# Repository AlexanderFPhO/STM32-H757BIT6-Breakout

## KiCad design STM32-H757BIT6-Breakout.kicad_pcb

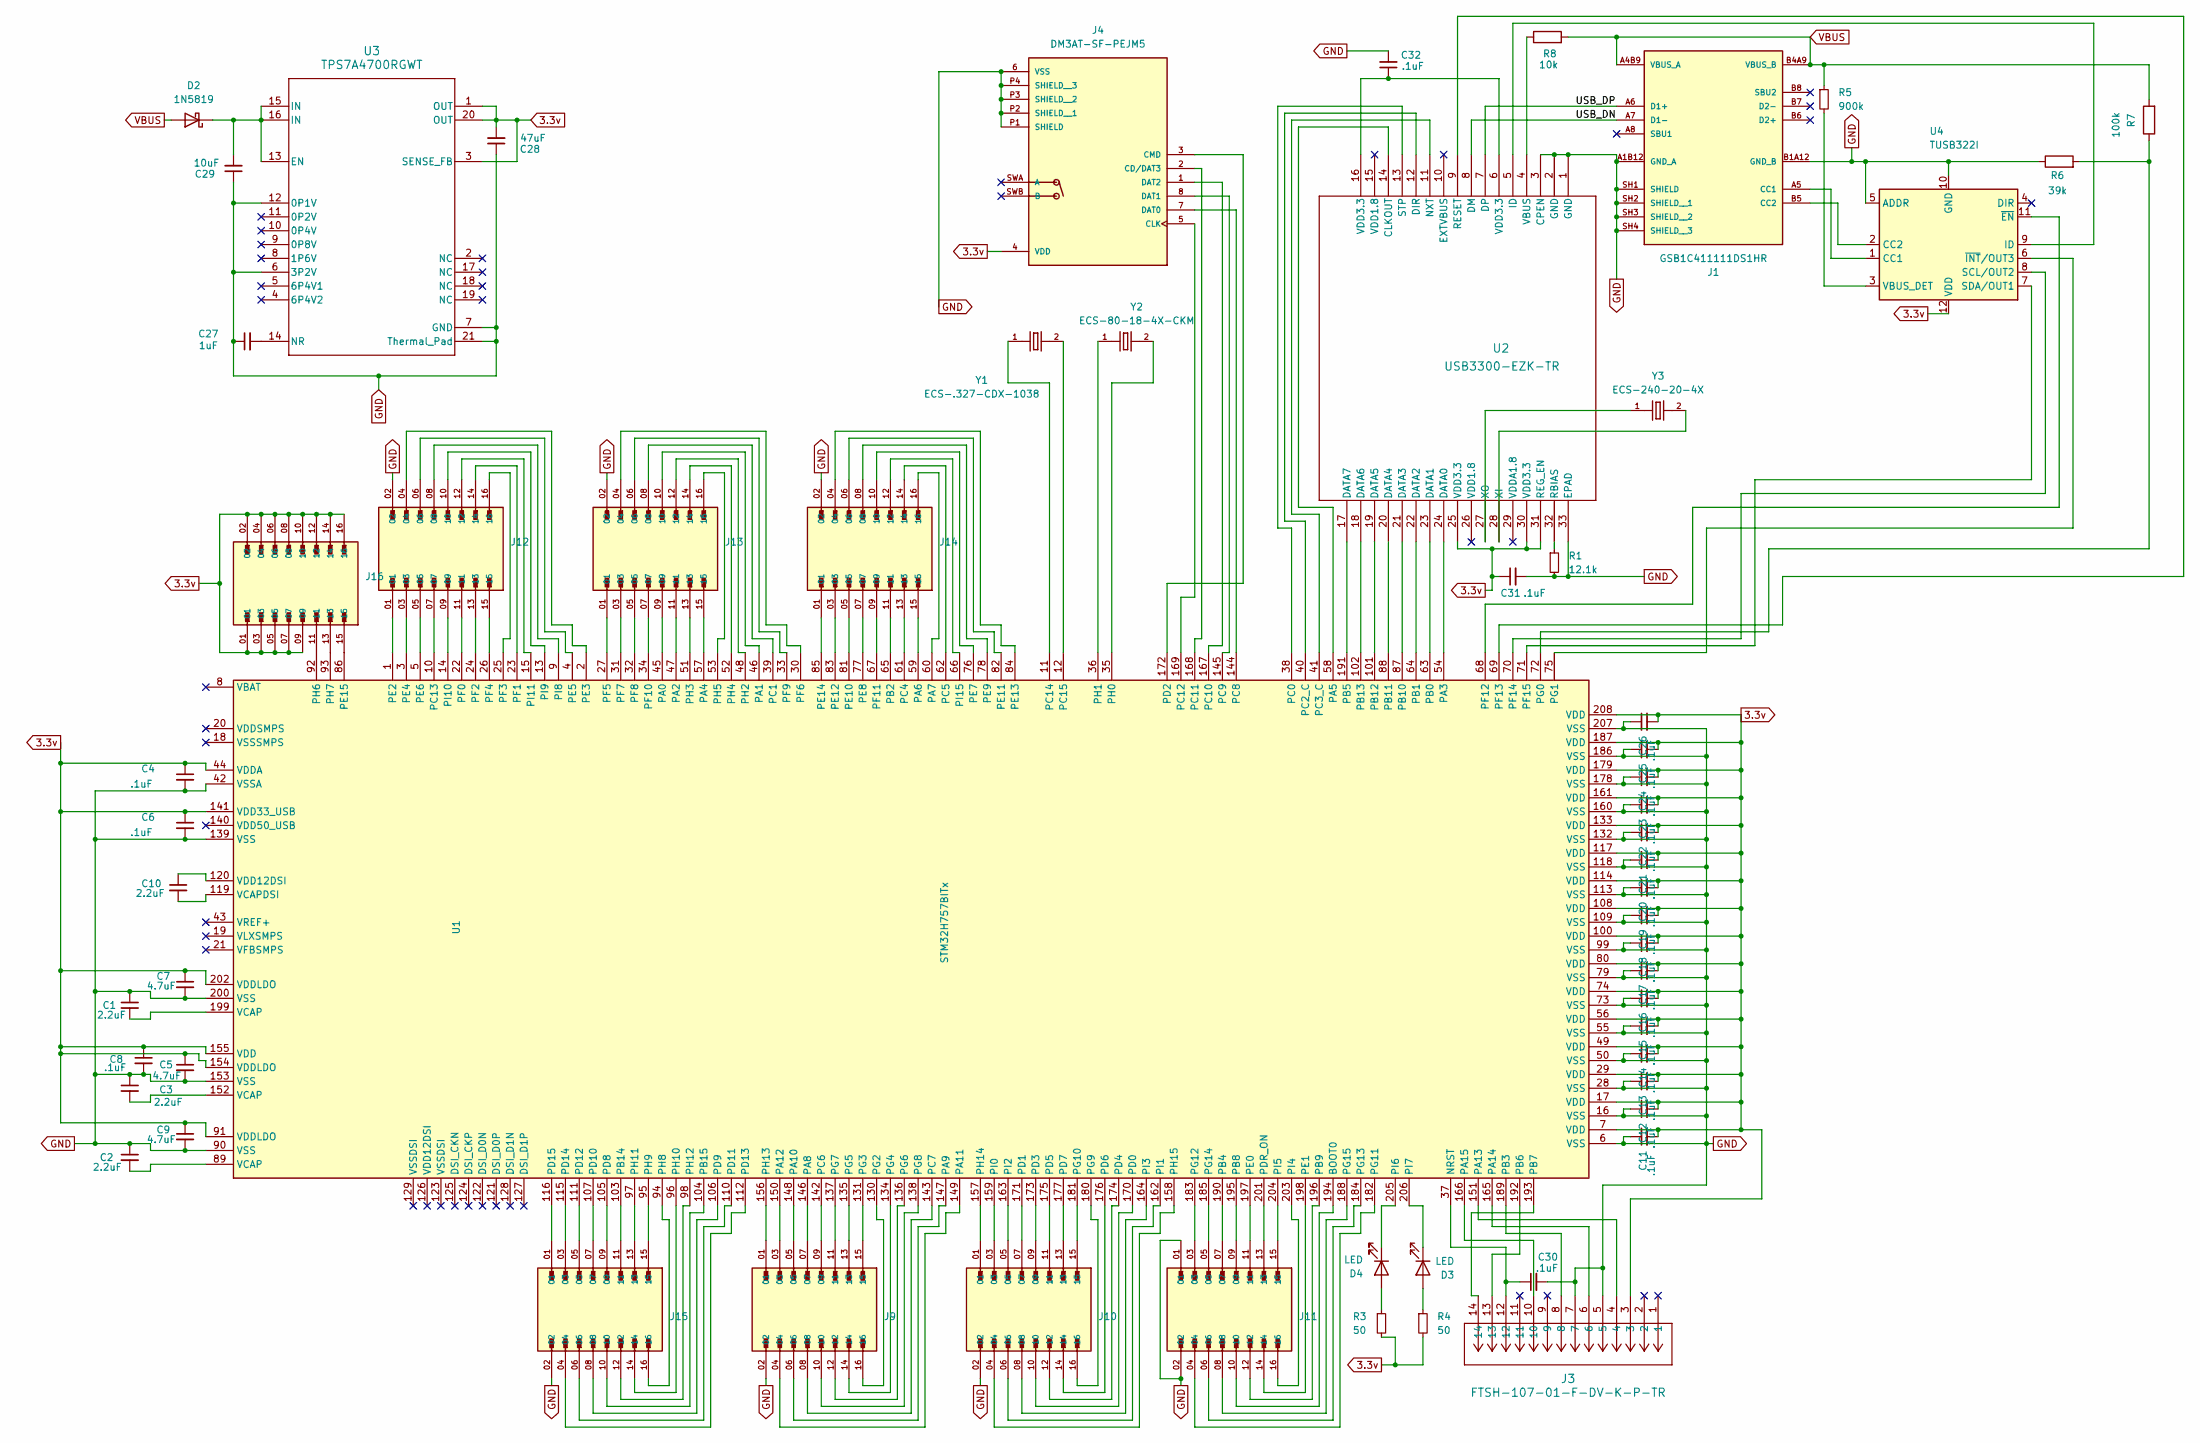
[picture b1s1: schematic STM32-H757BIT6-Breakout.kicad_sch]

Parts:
C1, C2, C3, C10: 2.2uF; C_0603_1608Metric_Pad1.08x0.95mm_HandSolder
C4, C6, C8, C11, C12, C13, C14, C15, C16, C17, C18, C19, C20, C21, C22, C23, C24, C25, C26, C30, C31, C32: .1uF; C_0603_1608Metric_Pad1.08x0.95mm_HandSolder
C5, C7, C9: 4.7uF; C_0603_1608Metric_Pad1.08x0.95mm_HandSolder
C27: 1uF; C_0603_1608Metric_Pad1.08x0.95mm_HandSolder
C28: 47uF; C_0603_1608Metric_Pad1.08x0.95mm_HandSolder
C29: 10uF; C_0603_1608Metric_Pad1.08x0.95mm_HandSolder
D2: 1N5819; D_DO-41_SOD81_P10.16mm_Horizontal
D3, D4: LED; LED_0603_1608Metric_Pad1.05x0.95mm_HandSolder
J1: GSB1C411111DS1HR; GSB1C411111DS1HR_AMPHENOL_GSB1C411111DS1HR; PARTREV AX3
J3: FTSH-107-01-F-DV-K-P-TR; CONN_FTSH-107-01-F-DV-K-P-TR_SAI
J4: DM3AT-SF-PEJM5; DM3AT-SF-PEJM5_HRS_DM3AT-SF-PEJM5; PARTREV 20200913
J9, J10, J11, J12, J13, J14, J15, J16: 10129381-916001BLF; PARTREV D
R1: 12.1k; R_0603_1608Metric_Pad0.98x0.95mm_HandSolder
R3, R4: 50; R_0603_1608Metric_Pad0.98x0.95mm_HandSolder
R5: 900k; R_0603_1608Metric_Pad0.98x0.95mm_HandSolder
R6: 39k; R_0603_1608Metric_Pad0.98x0.95mm_HandSolder
R7: 100k; R_0603_1608Metric_Pad0.98x0.95mm_HandSolder
R8: 10k; R_0603_1608Metric_Pad0.98x0.95mm_HandSolder
U1: STM32H757BITx; LQFP-208_28x28mm_P0.5mm
U2: USB3300-EZK-TR; QFN32_5X5MC_MCH
U3: TPS7A4700RGWT; RGW0020A-IPC_A
U4: TUSB322I; Texas_X2QFN-12_1.6x1.6mm_P0.4mm
Y1: ECS-.327-CDX-1038; ECS-.327-CDX-1038_XTAL_ECS-.327-CDX-1038
Y2: ECS-80-18-4X-CKM; ECS-80-18-4X-CKM_XTAL_ECS-80-18-4X-CKM
Y3: ECS-240-20-4X; ECS-240-20-4X_XTAL_ECS-240-20-4X

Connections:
3.3v: C4.1, C5.1, C6.1, C7.1, C8.1, C9.1, C11.2, C12.2, C13.2, C14.2, C15.2, C16.2, C17.2, C18.2, C19.2, C20.2, C21.2, C22.2, C23.2, C24.2, C25.2, C26.2, C28.2, C31.1, J3.3, J4.4 (VDD), J16.01, J16.02, J16.03, J16.04, J16.05, J16.06, J16.07, J16.08, J16.09, J16.10, J16.12, J16.14, J16.16, R3.2, R4.2, U1.7 (VDD), U1.17 (VDD), U1.29 (VDD), U1.44 (VDDA), U1.49 (VDD), U1.56 (VDD), U1.74 (VDD), U1.80 (VDD), U1.91 (VDDLDO), U1.100 (VDD), U1.108 (VDD), U1.114 (VDD), U1.117 (VDD), U1.133 (VDD), U1.141 (VDD33_USB), U1.154 (VDDLDO), U1.155 (VDD), U1.161 (VDD), U1.179 (VDD), U1.187 (VDD), U1.202 (VDDLDO), U1.208 (VDD), U2.25 (VDD3.3), U2.30 (VDD3.3), U2.31 (REG_EN), U3.1 (OUT), U3.3 (SENSE_FB), U3.20 (OUT), U4.12 (VDD)
/USB_DN: J1.A7 (D1-), U2.8 (DM)
/USB_DP: J1.A6 (D1+), U2.7 (DP)
GND: C1.1, C2.1, C3.1, C4.2, C5.2, C6.2, C7.2, C8.2, C9.2, C11.1, C12.1, C13.1, C14.1, C15.1, C16.1, C17.1, C18.1, C19.1, C20.1, C21.1, C22.1, C23.1, C24.1, C25.1, C26.1, C27.1, C28.1, C29.1, C30.2, C31.2, C32.2, J1.A1B12 (GND_A), J1.B1A12 (GND_B), J1.SH1 (SHIELD), J1.SH2 (SHIELD__1), J1.SH3 (SHIELD__2), J1.SH4 (SHIELD__3), J3.5, J3.7, J4.6 (VSS), J4.P1 (SHIELD), J4.P2 (SHIELD__1), J4.P3 (SHIELD__2), J4.P4 (SHIELD__3), J9.02, J10.02, J11.01, J11.02, J12.02, J13.02, J14.02, J15.02, R1.2, R6.1, U1.6 (VSS), U1.16 (VSS), U1.28 (VSS), U1.42 (VSSA), U1.50 (VSS), U1.55 (VSS), U1.73 (VSS), U1.79 (VSS), U1.90 (VSS), U1.99 (VSS), U1.109 (VSS), U1.113 (VSS), U1.118 (VSS), U1.132 (VSS), U1.139 (VSS), U1.153 (VSS), U1.160 (VSS), U1.178 (VSS), U1.186 (VSS), U1.200 (VSS), U1.207 (VSS), U2.1 (GND), U2.2 (GND), U2.3 (CPEN), U2.33 (EPAD), U3.6 (3P2V), U3.7 (GND), U3.12 (0P1V), U3.21 (Thermal_Pad), U4.5 (ADDR), U4.10 (GND)
unnamed: C1.2, U1.199 (VCAP)
unnamed: C2.2, U1.89 (VCAP)
unnamed: C3.2, U1.152 (VCAP)
unnamed: C10.1, U1.120 (VDD12DSI)
unnamed: C32.1, U2.6 (VDD3.3), U2.16 (VDD3.3)
unnamed: C29.2, D2.1 (K), U3.13 (EN), U3.15 (IN), U3.16 (IN)
unnamed: D3.2 (A), R4.1
unnamed: D3.1 (K), U1.206 (PI7)
unnamed: D4.2 (A), R3.1
unnamed: D4.1 (K), U1.205 (PI6)
unnamed: J1.A5 (CC1), U4.1 (CC1)
unnamed: J1.B5 (CC2), U4.2 (CC2)
unnamed: J4.2 (CD/DAT3), U1.168 (PC11)
unnamed: J4.5 (CLK), U1.169 (PC12)
unnamed: J4.3 (CMD), U1.172 (PD2)
unnamed: J4.7 (DAT0), U1.144 (PC8)
unnamed: J4.8 (DAT1), U1.145 (PC9)
unnamed: J4.1 (DAT2), U1.167 (PC10)
unnamed: J11.10, U1.194 (BOOT0)
unnamed: C30.1, J3.12, U1.37 (NRST)
unnamed: J13.09, U1.45 (PA0)
unnamed: J13.10, U1.46 (PA1)
unnamed: J13.11, U1.47 (PA2)
unnamed: U1.54 (PA3), U2.24 (DATA0)
unnamed: J13.15, U1.57 (PA4)
unnamed: U1.58 (PA5), U2.14 (CLKOUT)
unnamed: J14.15, U1.59 (PA6)
unnamed: J14.16, U1.60 (PA7)
unnamed: J9.07, U1.146 (PA8)
unnamed: J9.06, U1.147 (PA9)
unnamed: J9.05, U1.148 (PA10)
unnamed: J9.04, U1.149 (PA11)
unnamed: J9.03, U1.150 (PA12)
unnamed: J3.4, U1.151 (PA13)
unnamed: J3.6, U1.165 (PA14)
unnamed: J3.10, U1.166 (PA15)
unnamed: U1.63 (PB0), U2.23 (DATA1)
unnamed: U1.64 (PB1), U2.22 (DATA2)
unnamed: J14.11, U1.65 (PB2)
unnamed: J3.8, U1.189 (PB3)
unnamed: J11.07, U1.190 (PB4)
unnamed: U1.191 (PB5), U2.17 (DATA7)
unnamed: J3.13, U1.192 (PB6)
unnamed: J3.14, U1.193 (PB7)
unnamed: J11.09, U1.195 (PB8)
unnamed: J11.12, U1.196 (PB9)
unnamed: U1.87 (PB10), U2.21 (DATA3)
unnamed: U1.88 (PB11), U2.20 (DATA4)
unnamed: U1.101 (PB12), U2.19 (DATA5)
unnamed: U1.102 (PB13), U2.18 (DATA6)
unnamed: J15.11, U1.103 (PB14)
unnamed: J15.10, U1.104 (PB15)
unnamed: U1.38 (PC0), U2.13 (STP)
unnamed: J13.08, U1.39 (PC1)
unnamed: U1.40 (PC2_C), U2.12 (DIR)
unnamed: U1.41 (PC3_C), U2.11 (NXT)
unnamed: J14.13, U1.61 (PC4)
unnamed: J14.14, U1.62 (PC5)
unnamed: J9.09, U1.142 (PC6)
unnamed: J9.08, U1.143 (PC7)
unnamed: J12.07, U1.10 (PC13)
unnamed: U1.11 (PC14), Y1.1
unnamed: U1.12 (PC15), Y1.2
unnamed: J10.10, U1.170 (PD0)
unnamed: J10.07, U1.171 (PD1)
unnamed: J10.09, U1.173 (PD3)
unnamed: J10.12, U1.174 (PD4)
unnamed: J10.11, U1.175 (PD5)
unnamed: J10.14, U1.176 (PD6)
unnamed: J10.13, U1.177 (PD7)
unnamed: J15.09, U1.105 (PD8)
unnamed: J15.08, U1.106 (PD9)
unnamed: J15.07, U1.107 (PD10)
unnamed: J15.06, U1.110 (PD11)
unnamed: J15.05, U1.111 (PD12)
unnamed: J15.04, U1.112 (PD13)
unnamed: J15.03, U1.115 (PD14)
unnamed: J15.01, U1.116 (PD15)
unnamed: J11.13, U1.201 (PDR_ON)
unnamed: J11.11, U1.197 (PE0)
unnamed: J11.14, U1.198 (PE1)
unnamed: J12.01, U1.1 (PE2)
unnamed: J12.04, U1.2 (PE3)
unnamed: J12.03, U1.3 (PE4)
unnamed: J12.06, U1.4 (PE5)
unnamed: J12.05, U1.5 (PE6)
unnamed: J14.10, U1.76 (PE7)
unnamed: J14.07, U1.77 (PE8)
unnamed: J14.08, U1.78 (PE9)
unnamed: J14.05, U1.81 (PE10)
unnamed: J14.06, U1.82 (PE11)
unnamed: J14.03, U1.83 (PE12)
unnamed: J14.04, U1.84 (PE13)
unnamed: J14.01, U1.85 (PE14)
unnamed: J16.15, U1.86 (PE15)
unnamed: J12.11, U1.22 (PF0)
unnamed: J12.14, U1.23 (PF1)
unnamed: J12.13, U1.24 (PF2)
unnamed: J12.16, U1.25 (PF3)
unnamed: J12.15, U1.26 (PF4)
unnamed: J13.01, U1.27 (PF5)
unnamed: J13.04, U1.30 (PF6)
unnamed: J13.03, U1.31 (PF7)
unnamed: J13.05, U1.32 (PF8)
unnamed: J13.06, U1.33 (PF9)
unnamed: J13.07, U1.34 (PF10)
unnamed: J14.09, U1.67 (PF11)
unnamed: U1.68 (PF12), U4.11 (~EN)
unnamed: U1.69 (PF13), U2.9 (RESET)
unnamed: U1.70 (PF14), U4.8 (SCL/OUT2)
unnamed: U1.71 (PF15), U4.7 (SDA/OUT1)
unnamed: R6.2, R7.1, U1.72 (PG0)
unnamed: U1.75 (PG1), U4.6 (~INT/OUT3)
unnamed: J9.16, U1.130 (PG2)
unnamed: J9.15, U1.131 (PG3)
unnamed: J9.14, U1.134 (PG4)
unnamed: J9.13, U1.135 (PG5)
unnamed: J9.12, U1.136 (PG6)
unnamed: J9.11, U1.137 (PG7)
unnamed: J9.10, U1.138 (PG8)
unnamed: J10.16, U1.180 (PG9)
unnamed: J10.15, U1.181 (PG10)
unnamed: J11.04, U1.182 (PG11)
unnamed: J11.03, U1.183 (PG12)
unnamed: J11.06, U1.184 (PG13)
unnamed: J11.05, U1.185 (PG14)
unnamed: J11.08, U1.188 (PG15)
unnamed: U1.35 (PH0), Y2.2
unnamed: U1.36 (PH1), Y2.1
unnamed: J13.12, U1.48 (PH2)
unnamed: J13.13, U1.51 (PH3)
unnamed: J13.14, U1.52 (PH4)
unnamed: J13.16, U1.53 (PH5)
unnamed: J16.11, U1.92 (PH6)
unnamed: J16.13, U1.93 (PH7)
unnamed: J15.16, U1.94 (PH8)
unnamed: J15.15, U1.95 (PH9)
unnamed: J15.14, U1.96 (PH10)
unnamed: J15.13, U1.97 (PH11)
unnamed: J15.12, U1.98 (PH12)
unnamed: J9.01, U1.156 (PH13)
unnamed: J10.01, U1.157 (PH14)
unnamed: J10.04, U1.158 (PH15)
unnamed: J10.03, U1.159 (PI0)
unnamed: J10.06, U1.162 (PI1)
unnamed: J10.05, U1.163 (PI2)
unnamed: J10.08, U1.164 (PI3)
unnamed: J11.16, U1.203 (PI4)
unnamed: J11.15, U1.204 (PI5)
unnamed: J12.08, U1.9 (PI8)
unnamed: J12.10, U1.13 (PI9)
unnamed: J12.09, U1.14 (PI10)
unnamed: J12.12, U1.15 (PI11)
unnamed: J14.12, U1.66 (PI15)
unnamed: C10.2, U1.119 (VCAPDSI)
unnamed: U2.5 (ID), U4.9 (ID)
unnamed: R1.1, U2.32 (RBIAS)
unnamed: R8.1, U2.4 (VBUS)
unnamed: U2.28 (XI), Y3.2
unnamed: U2.27 (XO), Y3.1
unnamed: C27.2, U3.14 (NR)
unnamed: R5.2, U4.3 (VBUS_DET)
VBUS: D2.2 (A), J1.A4B9 (VBUS_A), J1.B4A9 (VBUS_B), R5.1, R7.2, R8.2

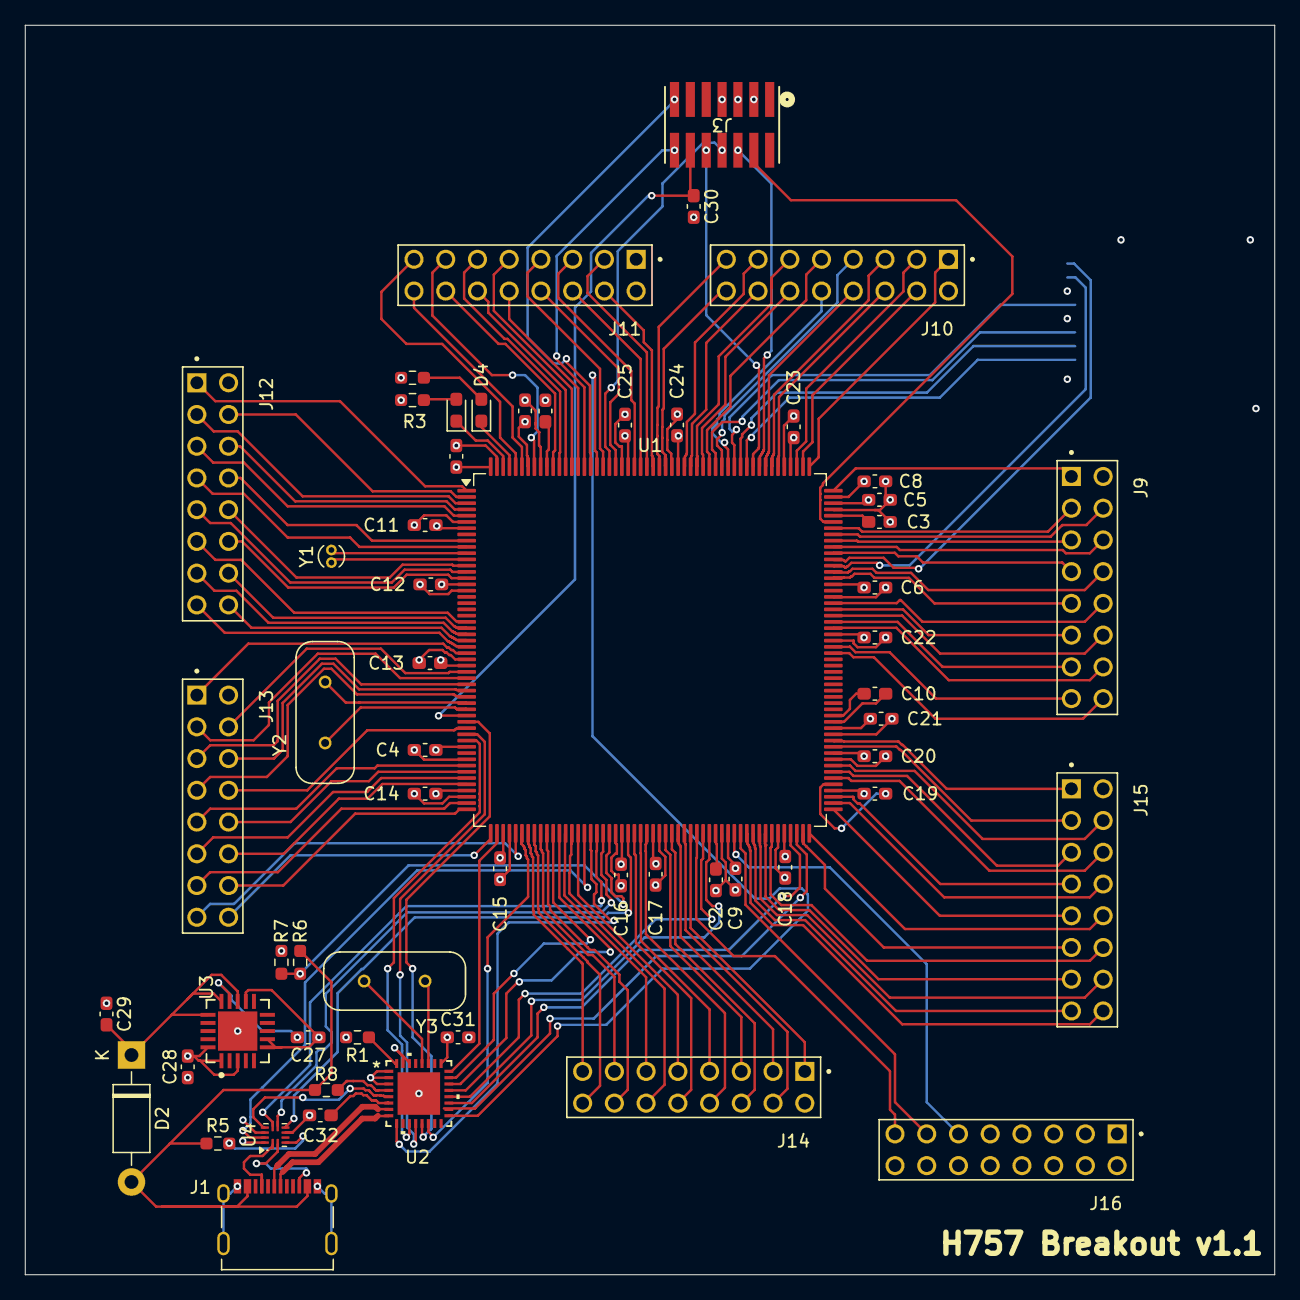
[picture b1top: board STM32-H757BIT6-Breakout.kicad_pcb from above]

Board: 4 copper layers, 100.0 x 100.0 mm, 60 parts (1 on the bottom side), 167 nets.

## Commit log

2025-04-23 v1.1
